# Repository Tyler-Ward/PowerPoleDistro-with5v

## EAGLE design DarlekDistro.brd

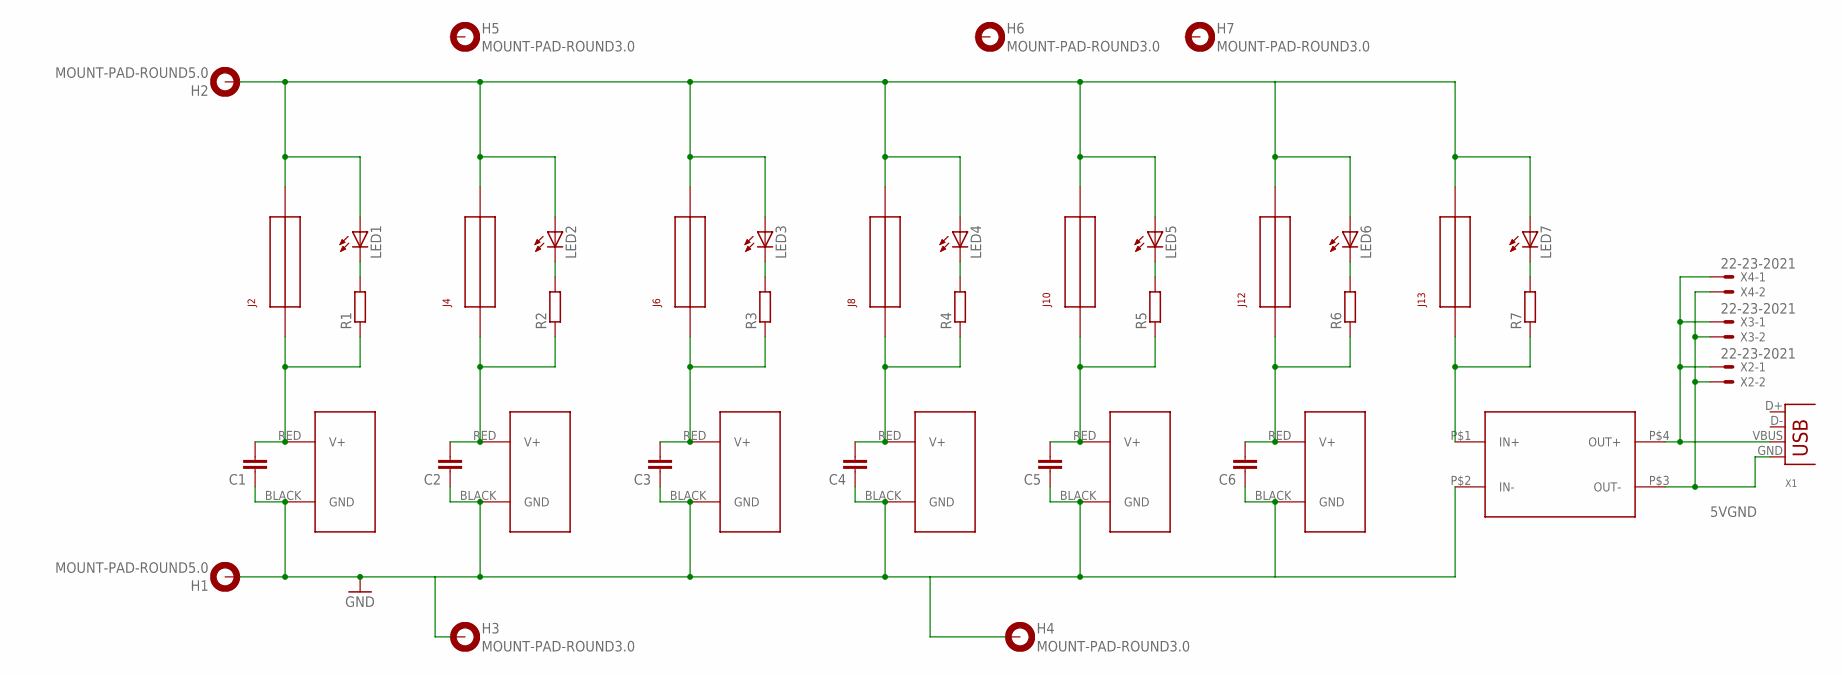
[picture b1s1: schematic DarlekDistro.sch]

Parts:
C1, C2, C3, C4, C5, C6: C-EU050-025X075; C050-025X075
H1, H2: MOUNT-PAD-ROUND5.0; 5,0-PAD
H3, H4, H5, H6, H7: MOUNT-PAD-ROUND3.0; 3,0-PAD
J1, J3, J5, J7, J9, J11: POWERPOLE_POWER10AWG; POWERPOLE_PAIR_10AWG
J2, J4, J6, J8, J10, J12, J13: FUSEATC; FUSE_ATC
LED1, LED2, LED3, LED4, LED5, LED6, LED7: LED3MM
R1, R2, R3, R4, R5, R6, R7: R-EU_0204/7; 0204/7
U$1: DSN2596_REG
X1: USB-A-H
X2, X3, X4: 22-23-2021

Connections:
5VGND: U$1.P$3 (OUT-), X1.GND, X2.2, X3.2, X4.2
GND: C1.1, C2.1, C3.1, C4.1, C5.1, C6.1, H1.B5, H3.B3,0, H4.B3,0, J1.BLACK (GND), J3.BLACK (GND), J5.BLACK (GND), J7.BLACK (GND), J9.BLACK (GND), J11.BLACK (GND), U$1.P$2 (IN-)
unnamed: LED2.K (C), R2.2
unnamed: LED1.K (C), R1.2
unnamed: LED3.K (C), R3.2
unnamed: LED4.K (C), R4.2
unnamed: LED5.K (C), R5.2
unnamed: LED6.K (C), R6.2
unnamed: LED7.K (C), R7.2
unnamed: U$1.P$4 (OUT+), X1.VBUS, X2.1, X3.1, X4.1
PPV1: C1.2, J1.RED (V+), J2.P$1, J2.P$2, R1.1
PPV2: C2.2, J3.RED (V+), J4.P$1, J4.P$2, R2.1
PPV3: C3.2, J5.RED (V+), J6.P$1, J6.P$2, R3.1
PPV4: C4.2, J7.RED (V+), J8.P$1, J8.P$2, R4.1
PPV5: C5.2, J9.RED (V+), J10.P$1, J10.P$2, R5.1
PPV6: C6.2, J11.RED (V+), J12.P$1, J12.P$2, R6.1
PPV7: J13.P$1, J13.P$2, R7.1, U$1.P$1 (IN+)
VCC: H2.B5, J2.P$3, J2.P$4, J4.P$3, J4.P$4, J6.P$3, J6.P$4, J8.P$3, J8.P$4, J10.P$3, J10.P$4, J12.P$3, J12.P$4, J13.P$3, J13.P$4, LED1.A, LED2.A, LED3.A, LED4.A, LED5.A, LED6.A, LED7.A

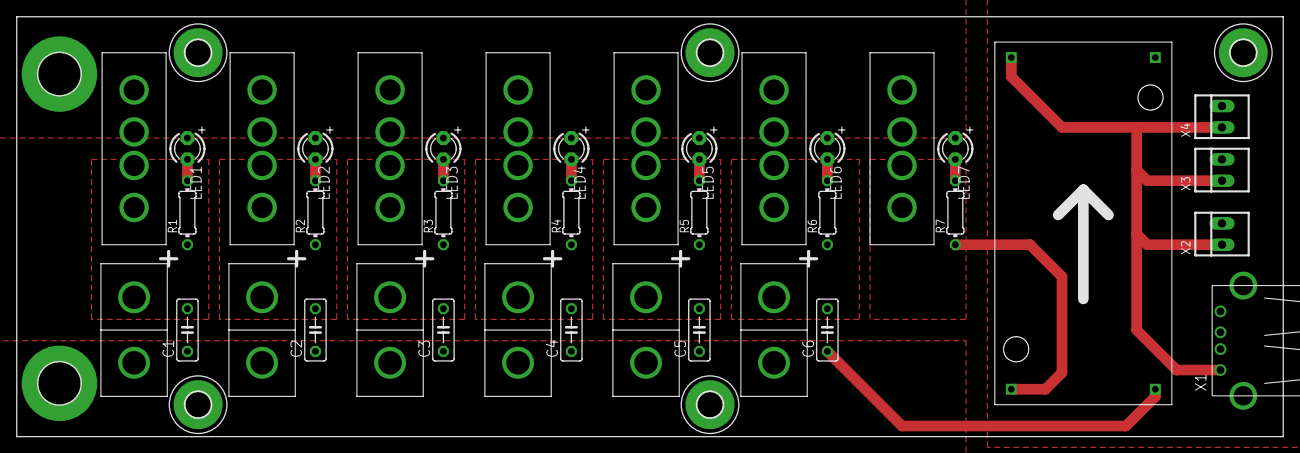
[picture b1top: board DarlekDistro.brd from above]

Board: 2 copper layers, 150.8 x 50.0 mm, 45 parts (0 on the bottom side), 18 nets.

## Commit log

2014-04-19 added draft version of powerpole distro board
2015-07-11 Renamed files for use with Darlek
2015-07-11 Added 5v reg and connectors
2015-07-18 Modified to require only single layer etching
